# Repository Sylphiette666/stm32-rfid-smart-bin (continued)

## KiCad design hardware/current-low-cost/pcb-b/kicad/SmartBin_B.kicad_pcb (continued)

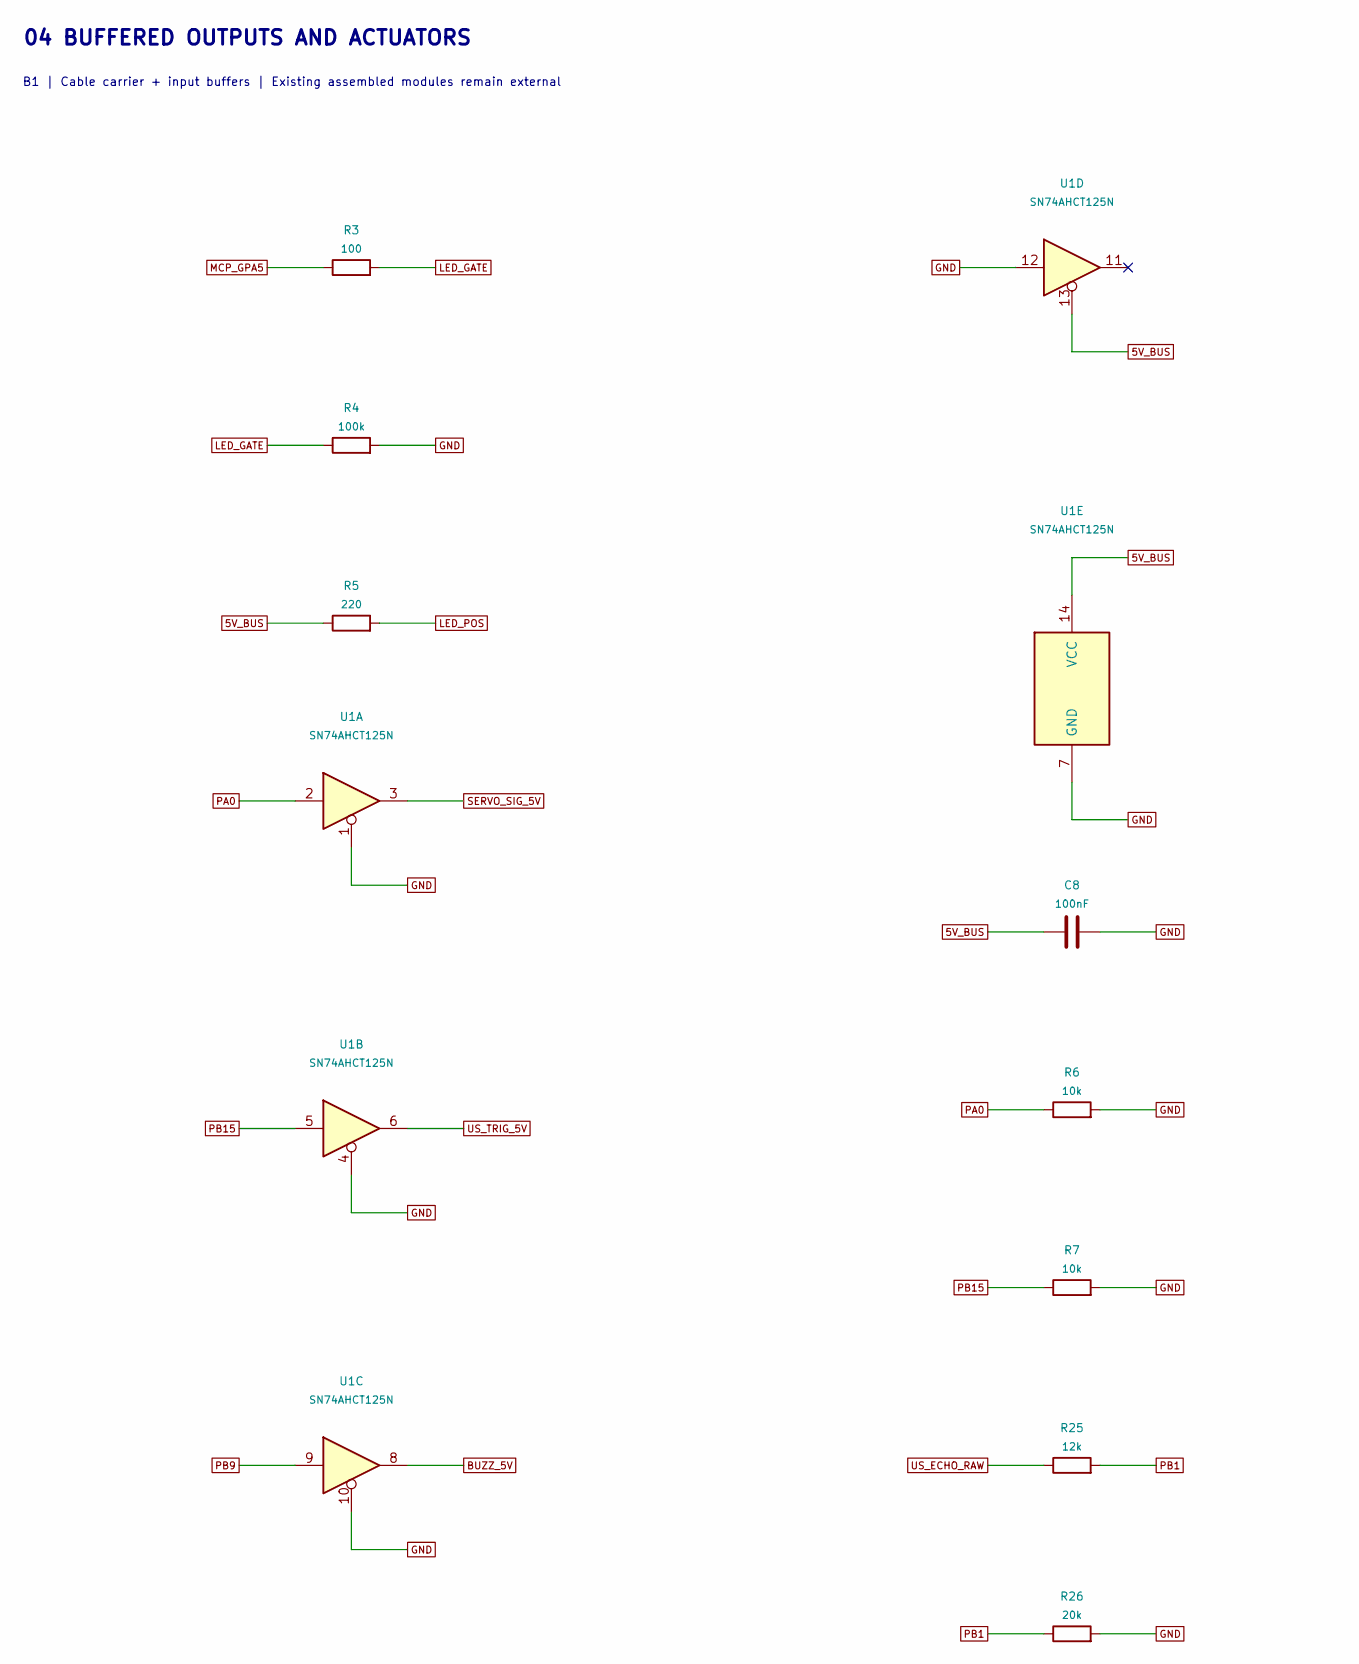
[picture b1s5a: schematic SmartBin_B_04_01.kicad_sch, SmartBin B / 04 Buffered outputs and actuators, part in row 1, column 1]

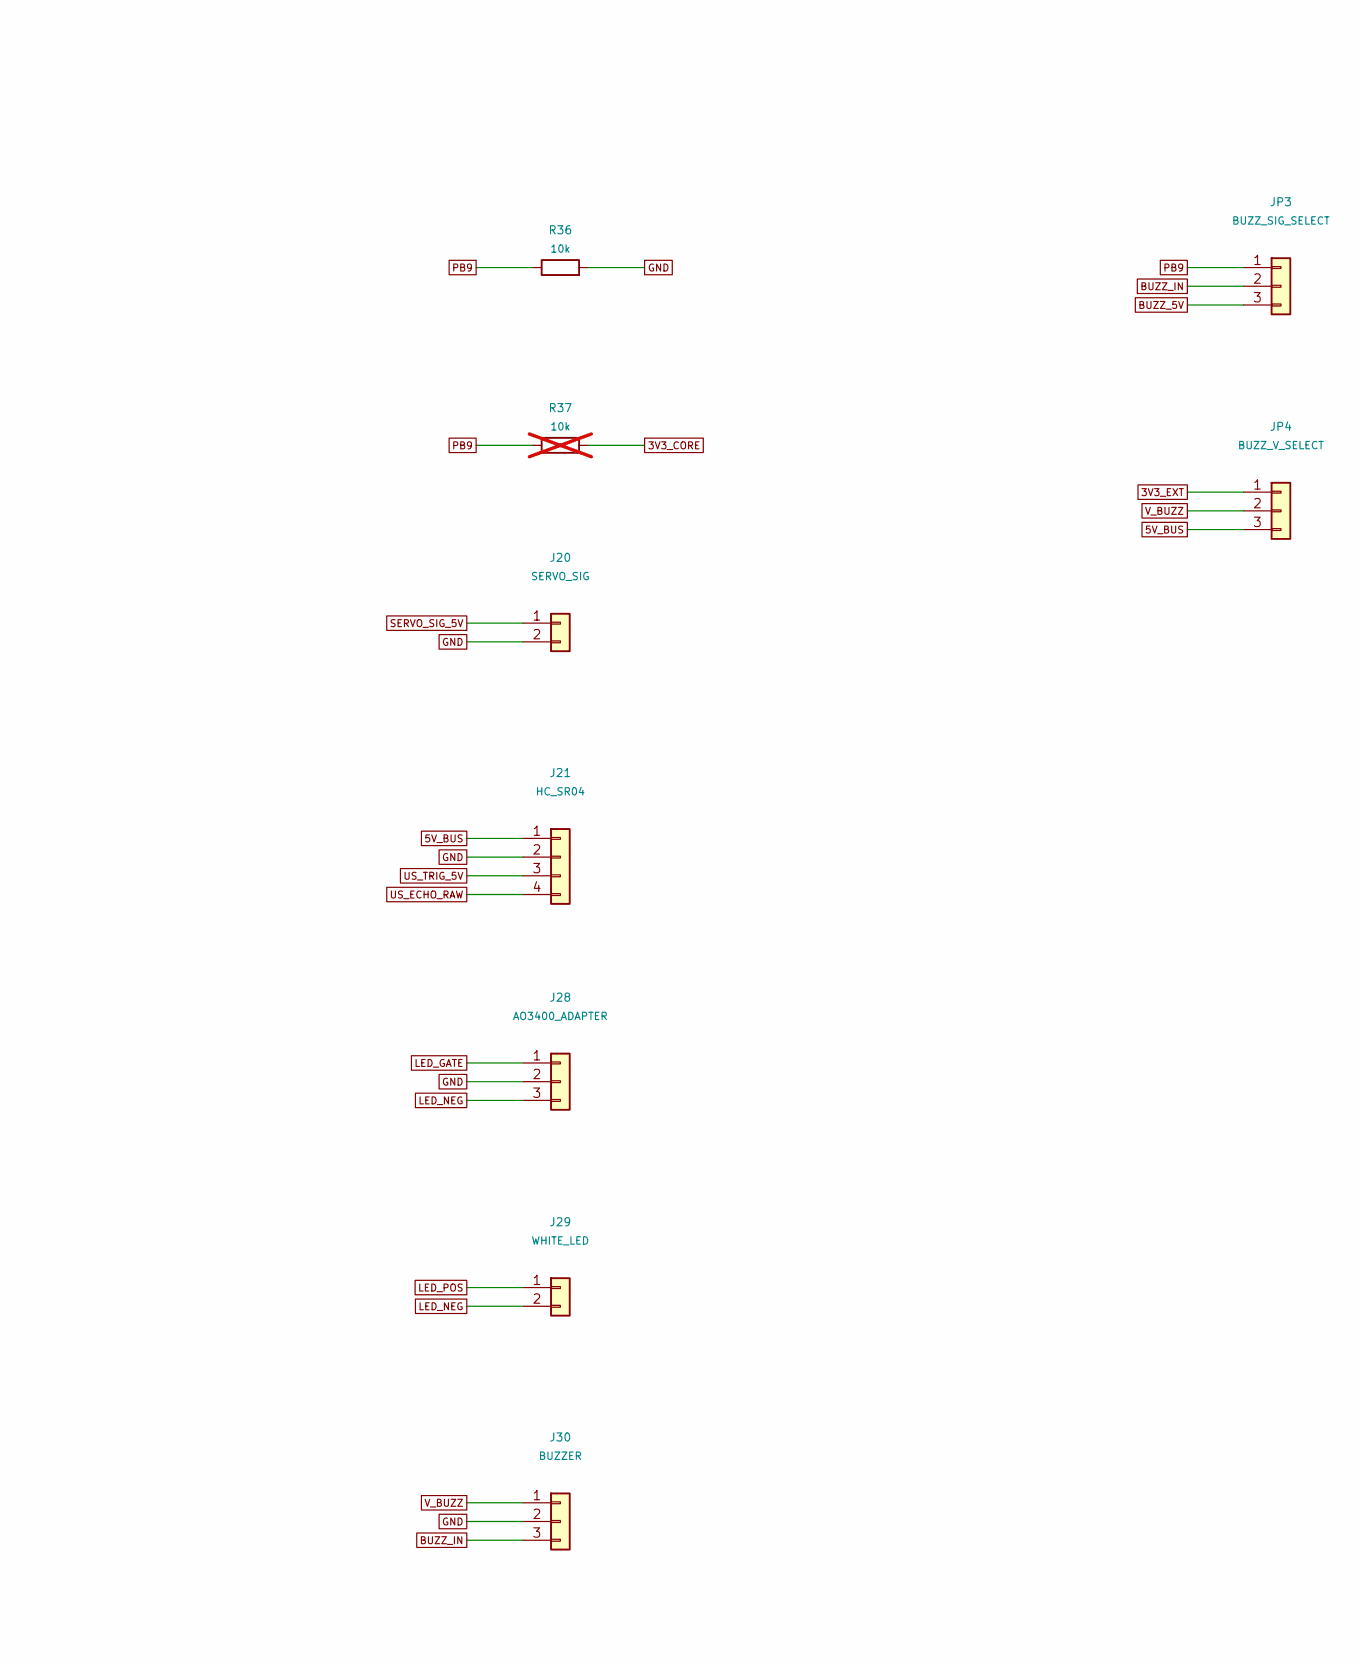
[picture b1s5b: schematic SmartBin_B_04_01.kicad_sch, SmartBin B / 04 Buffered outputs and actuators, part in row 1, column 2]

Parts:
C8: 100nF; C_Disc_D5.0mm_W2.5mm_P5.00mm
J20: SERVO_SIG; PinHeader_1x02_P2.54mm_Vertical
J21: HC_SR04; PinHeader_1x04_P2.54mm_Vertical
J28: AO3400_ADAPTER; PinHeader_1x03_P2.54mm_Vertical
J29: WHITE_LED; PinHeader_1x02_P2.54mm_Vertical
J30: BUZZER; PinHeader_1x03_P2.54mm_Vertical
JP3: BUZZ_SIG_SELECT; PinHeader_1x03_P2.54mm_Vertical
JP4: BUZZ_V_SELECT; PinHeader_1x03_P2.54mm_Vertical
R3: 100; R_Axial_DIN0207_L6.3mm_D2.5mm_P10.16mm_Horizontal
R4: 100k; R_Axial_DIN0207_L6.3mm_D2.5mm_P10.16mm_Horizontal
R5: 220; R_Axial_DIN0207_L6.3mm_D2.5mm_P10.16mm_Horizontal
R6, R7, R36: 10k; R_Axial_DIN0207_L6.3mm_D2.5mm_P10.16mm_Horizontal
R25: 12k; R_Axial_DIN0207_L6.3mm_D2.5mm_P10.16mm_Horizontal
R26: 20k; R_Axial_DIN0207_L6.3mm_D2.5mm_P10.16mm_Horizontal
R37: 10k; R_Axial_DIN0207_L6.3mm_D2.5mm_P10.16mm_Horizontal; not fitted
U1: SN74AHCT125N; DIP-14_W7.62mm_Socket

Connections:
3V3_CORE: R37.2; also elsewhere on the board
3V3_EXT: JP4.1; also elsewhere on the board
5V_BUS: C8.1, J21.1, JP4.3, R5.1, U1.13, U1.14 (VCC); also elsewhere on the board
BUZZ_5V: JP3.3, U1.8
BUZZ_IN: J30.3, JP3.2
GND: C8.2, J20.2, J21.2, J28.2, J30.2, R4.2, R6.2, R7.2, R26.2, R36.2, U1.1, U1.4, U1.7 (GND), U1.10, U1.12; also elsewhere on the board
LED_GATE: J28.1, R3.2, R4.1
LED_NEG: J28.3, J29.2
LED_POS: J29.1, R5.2
MCP_GPA5: R3.1; also elsewhere on the board
PA0: R6.1, U1.2; also elsewhere on the board
PB1: R25.2, R26.1; also elsewhere on the board
PB9: JP3.1, R36.1, R37.1, U1.9; also elsewhere on the board
PB15: R7.1, U1.5; also elsewhere on the board
SERVO_SIG_5V: J20.1, U1.3
US_ECHO_RAW: J21.4, R25.1
US_TRIG_5V: J21.3, U1.6
V_BUZZ: J30.1, JP4.2

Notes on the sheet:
04 BUFFERED OUTPUTS AND ACTUATORS
B1 | Cable carrier + input buffers | Existing assembled modules remain external

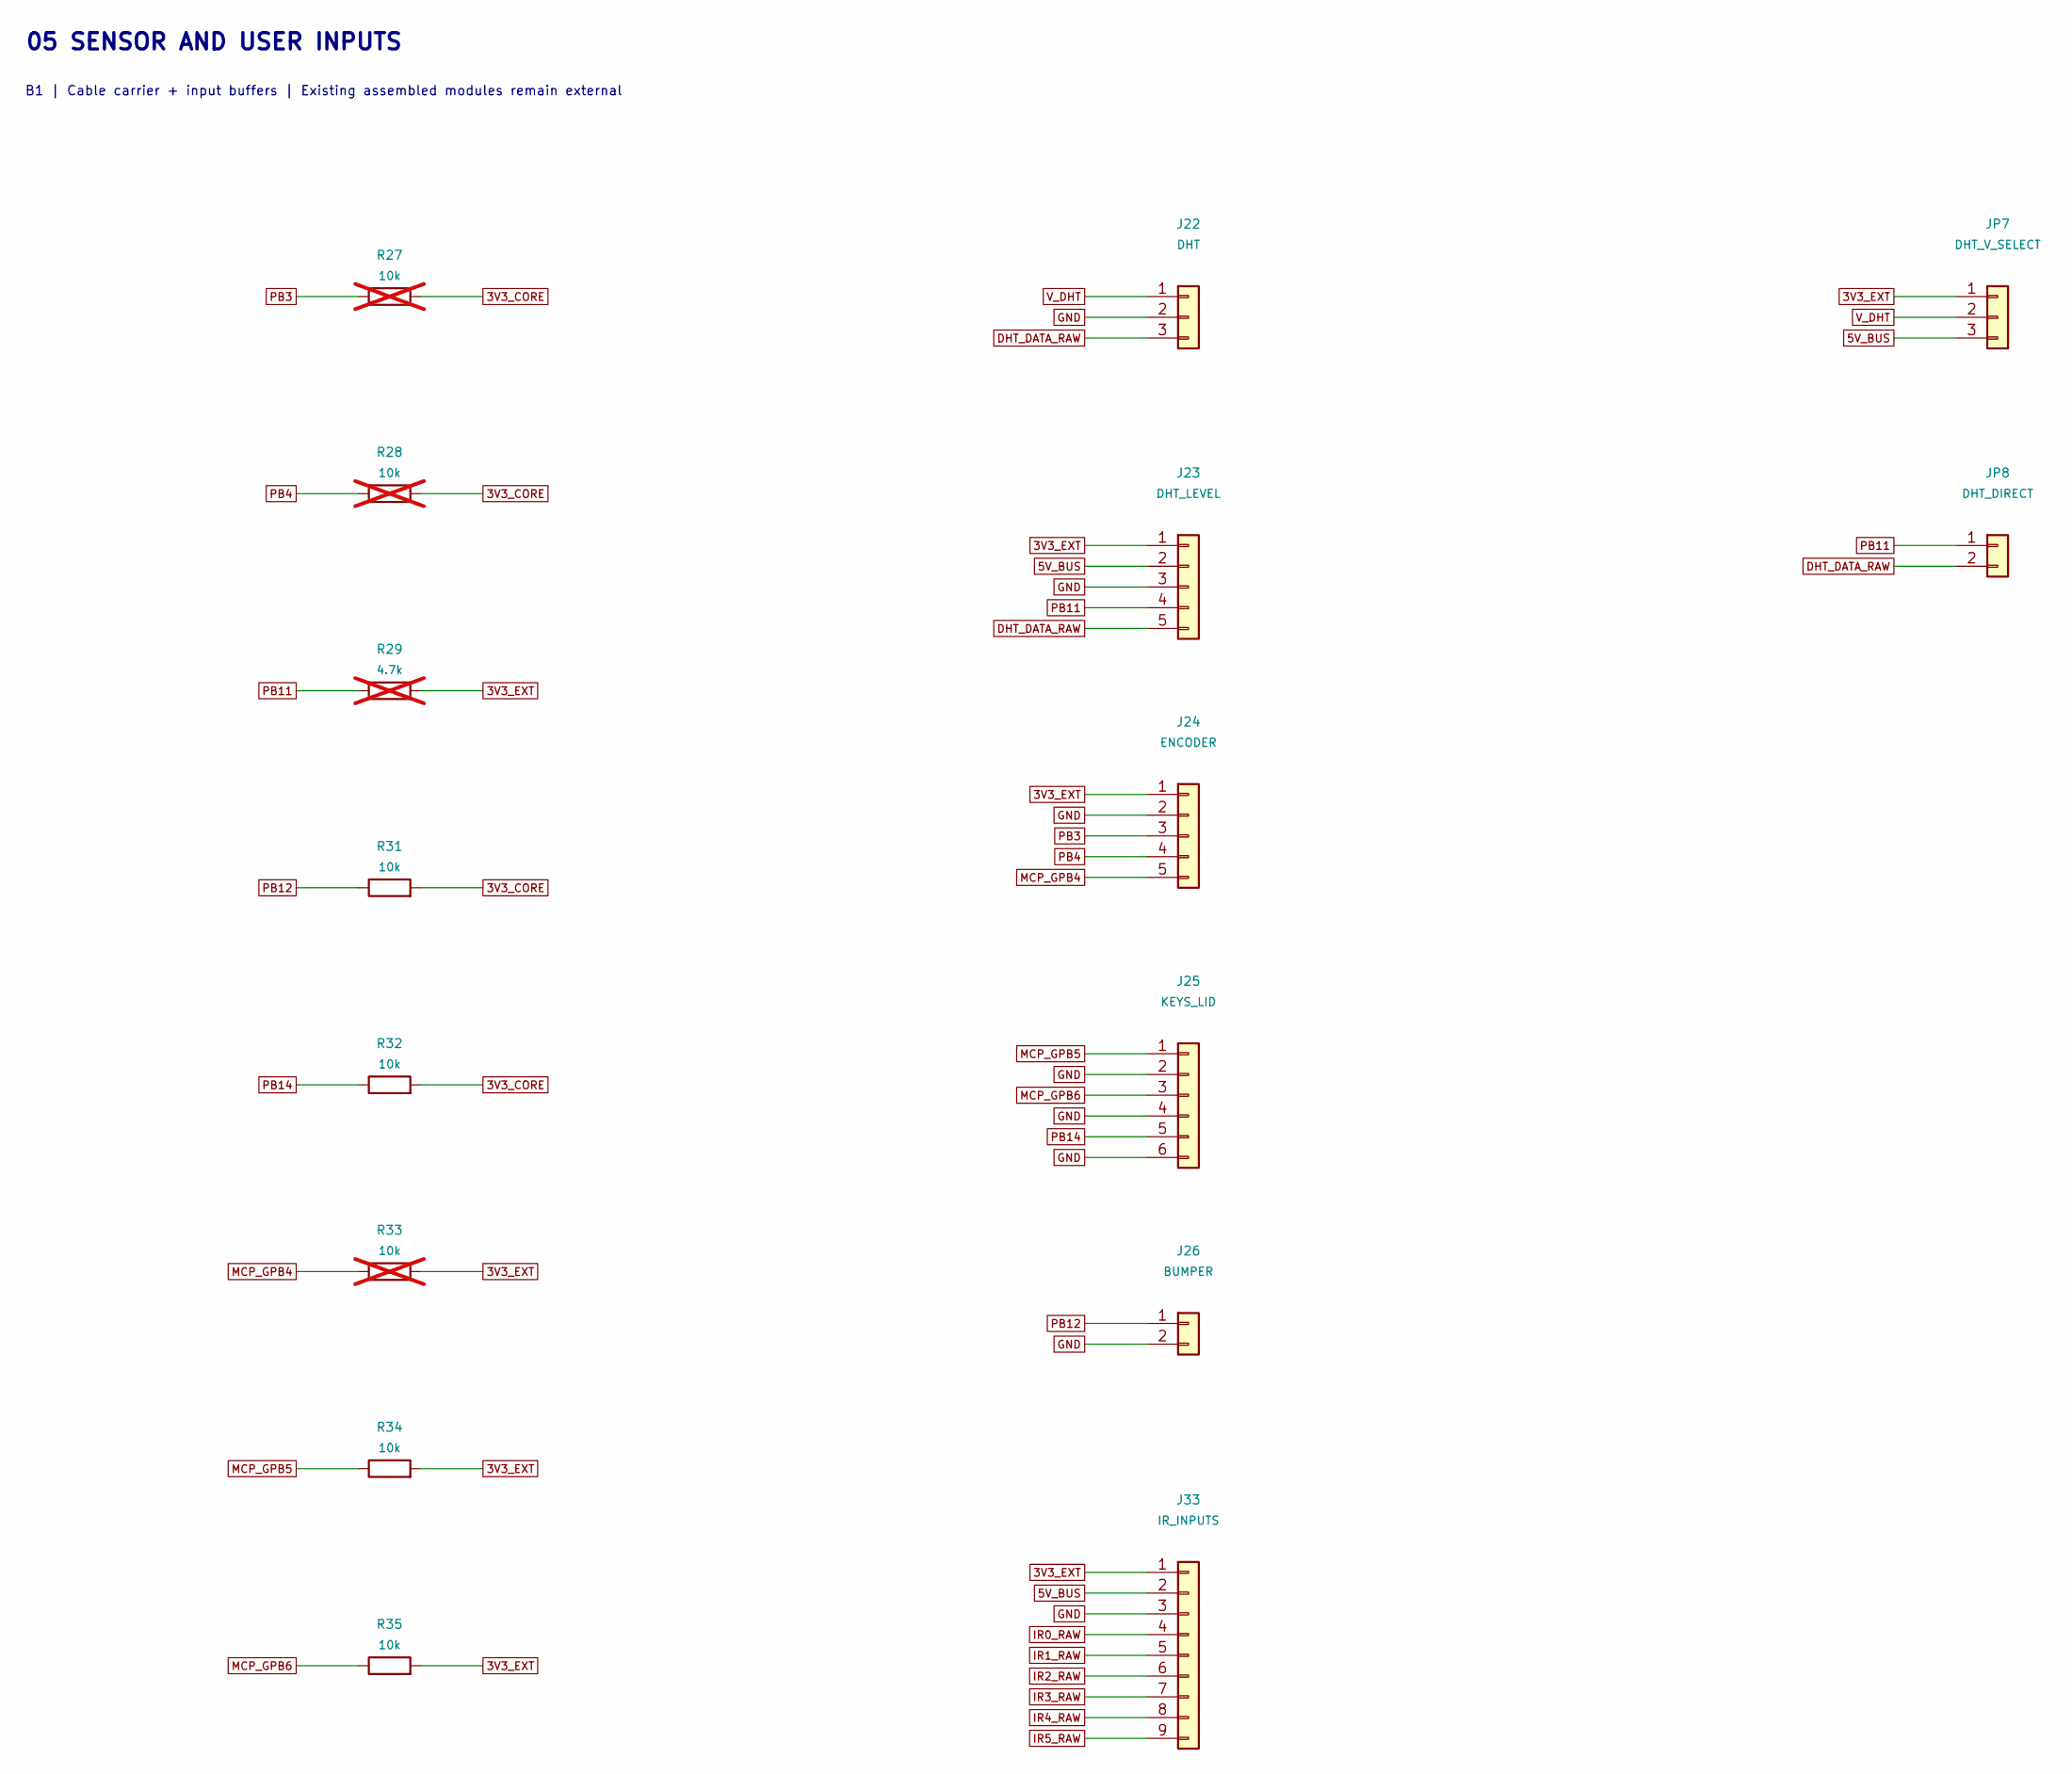
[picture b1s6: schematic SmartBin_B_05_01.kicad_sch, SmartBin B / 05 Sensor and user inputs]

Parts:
J22: DHT; PinHeader_1x03_P2.54mm_Vertical
J23: DHT_LEVEL; PinHeader_1x05_P2.54mm_Vertical
J24: ENCODER; PinHeader_1x05_P2.54mm_Vertical
J25: KEYS_LID; PinHeader_1x06_P2.54mm_Vertical
J26: BUMPER; PinHeader_1x02_P2.54mm_Vertical
J33: IR_INPUTS; PinHeader_1x09_P2.54mm_Vertical
JP7: DHT_V_SELECT; PinHeader_1x03_P2.54mm_Vertical
JP8: DHT_DIRECT; PinHeader_1x02_P2.54mm_Vertical
R27, R28, R33: 10k; R_Axial_DIN0207_L6.3mm_D2.5mm_P10.16mm_Horizontal; not fitted
R29: 4.7k; R_Axial_DIN0207_L6.3mm_D2.5mm_P10.16mm_Horizontal; not fitted
R31, R32, R34, R35: 10k; R_Axial_DIN0207_L6.3mm_D2.5mm_P10.16mm_Horizontal

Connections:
3V3_CORE: R27.2, R28.2, R31.2, R32.2; also elsewhere on the board
3V3_EXT: J23.1, J24.1, J33.1, JP7.1, R29.2, R33.2, R34.2, R35.2; also elsewhere on the board
5V_BUS: J23.2, J33.2, JP7.3; also elsewhere on the board
DHT_DATA_RAW: J22.3, J23.5, JP8.2
GND: J22.2, J23.3, J24.2, J25.2, J25.4, J25.6, J26.2, J33.3; also elsewhere on the board
IR0_RAW: J33.4; also elsewhere on the board
IR1_RAW: J33.5; also elsewhere on the board
IR2_RAW: J33.6; also elsewhere on the board
IR3_RAW: J33.7; also elsewhere on the board
IR4_RAW: J33.8; also elsewhere on the board
IR5_RAW: J33.9; also elsewhere on the board
MCP_GPB4: J24.5, R33.1; also elsewhere on the board
MCP_GPB5: J25.1, R34.1; also elsewhere on the board
MCP_GPB6: J25.3, R35.1; also elsewhere on the board
PB3: J24.3, R27.1; also elsewhere on the board
PB4: J24.4, R28.1; also elsewhere on the board
PB11: J23.4, JP8.1, R29.1; also elsewhere on the board
PB12: J26.1, R31.1; also elsewhere on the board
PB14: J25.5, R32.1; also elsewhere on the board
V_DHT: J22.1, JP7.2

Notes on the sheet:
05 SENSOR AND USER INPUTS
B1 | Cable carrier + input buffers | Existing assembled modules remain external

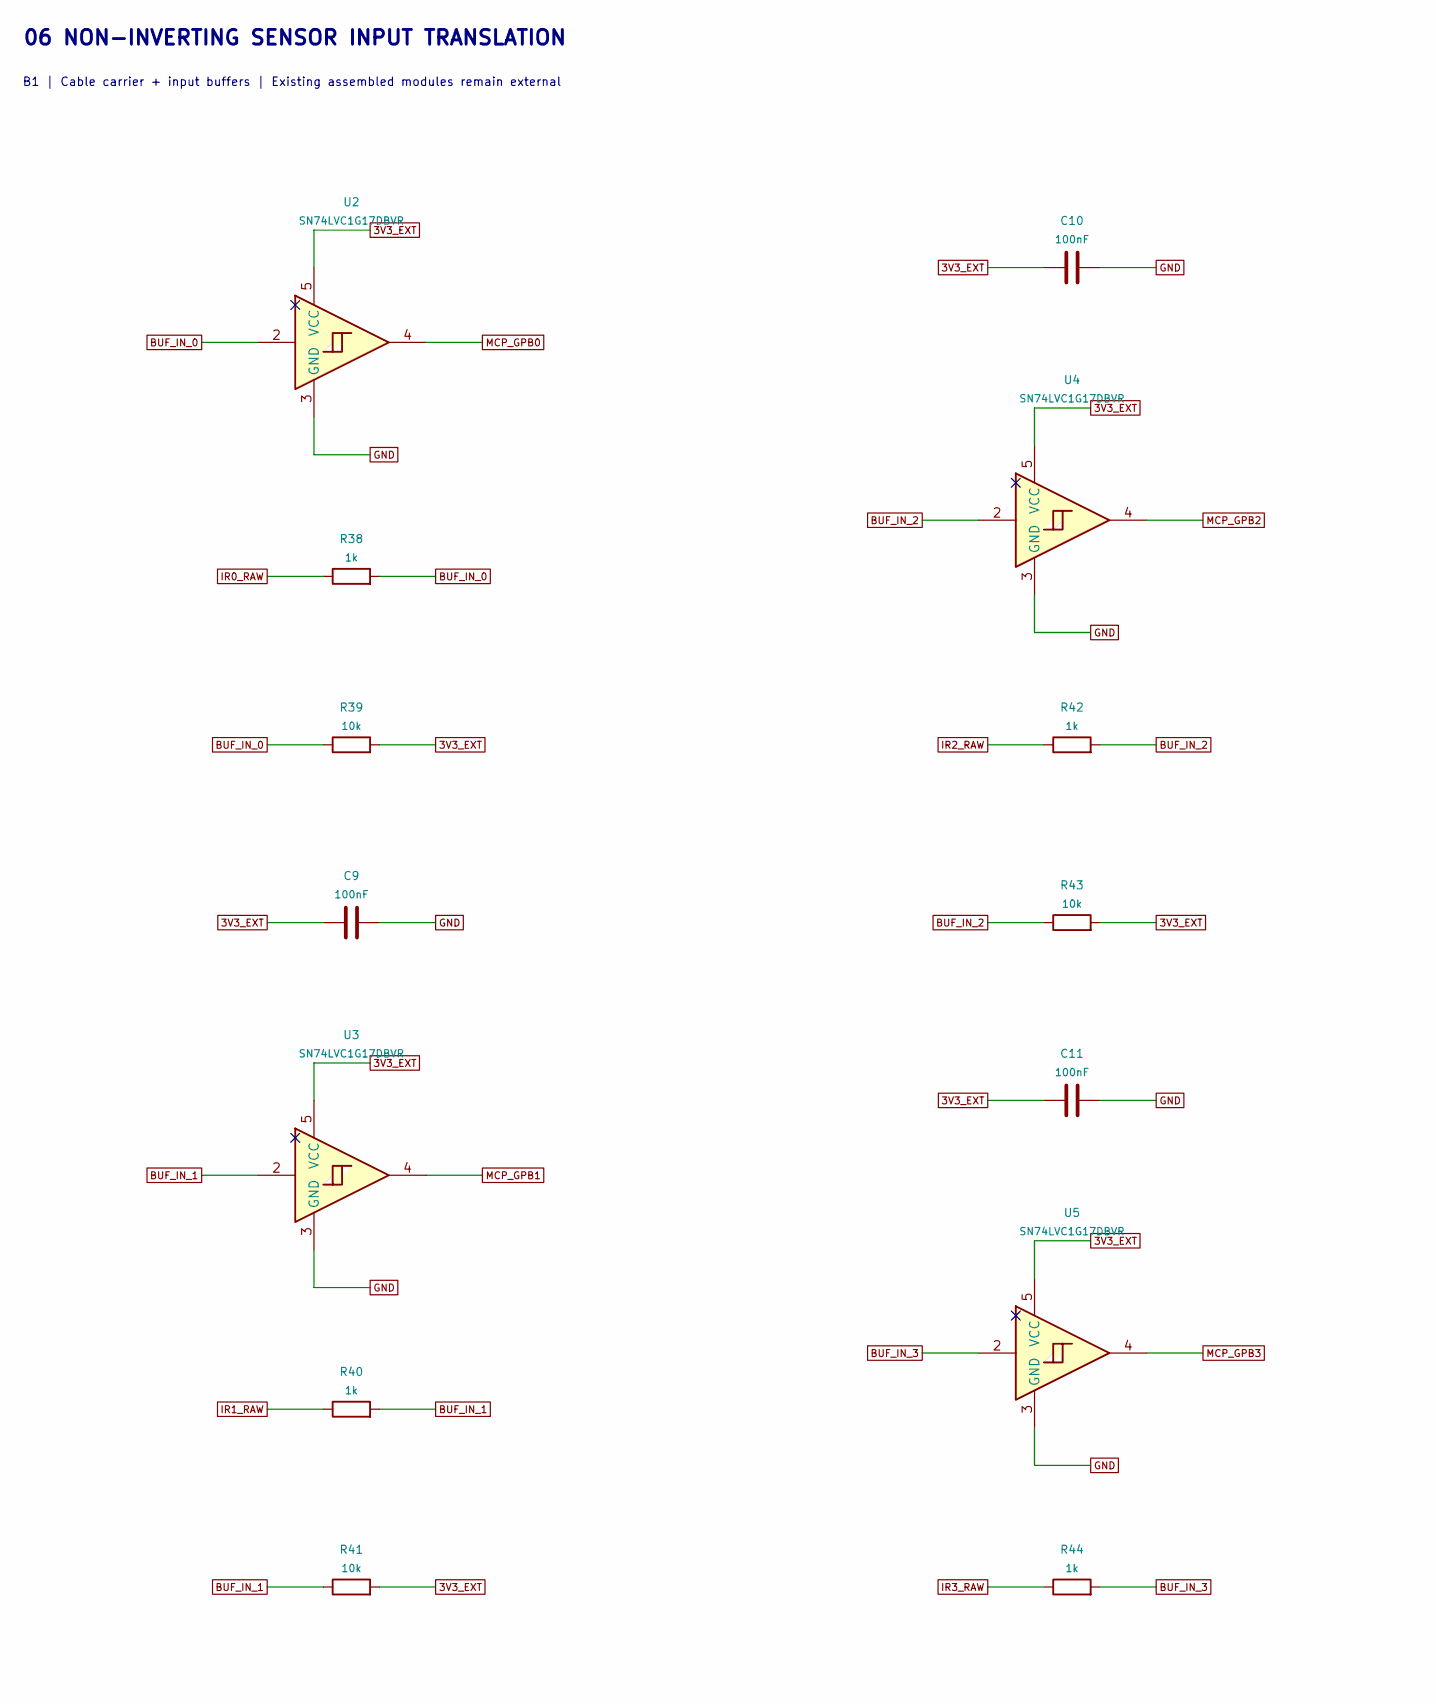
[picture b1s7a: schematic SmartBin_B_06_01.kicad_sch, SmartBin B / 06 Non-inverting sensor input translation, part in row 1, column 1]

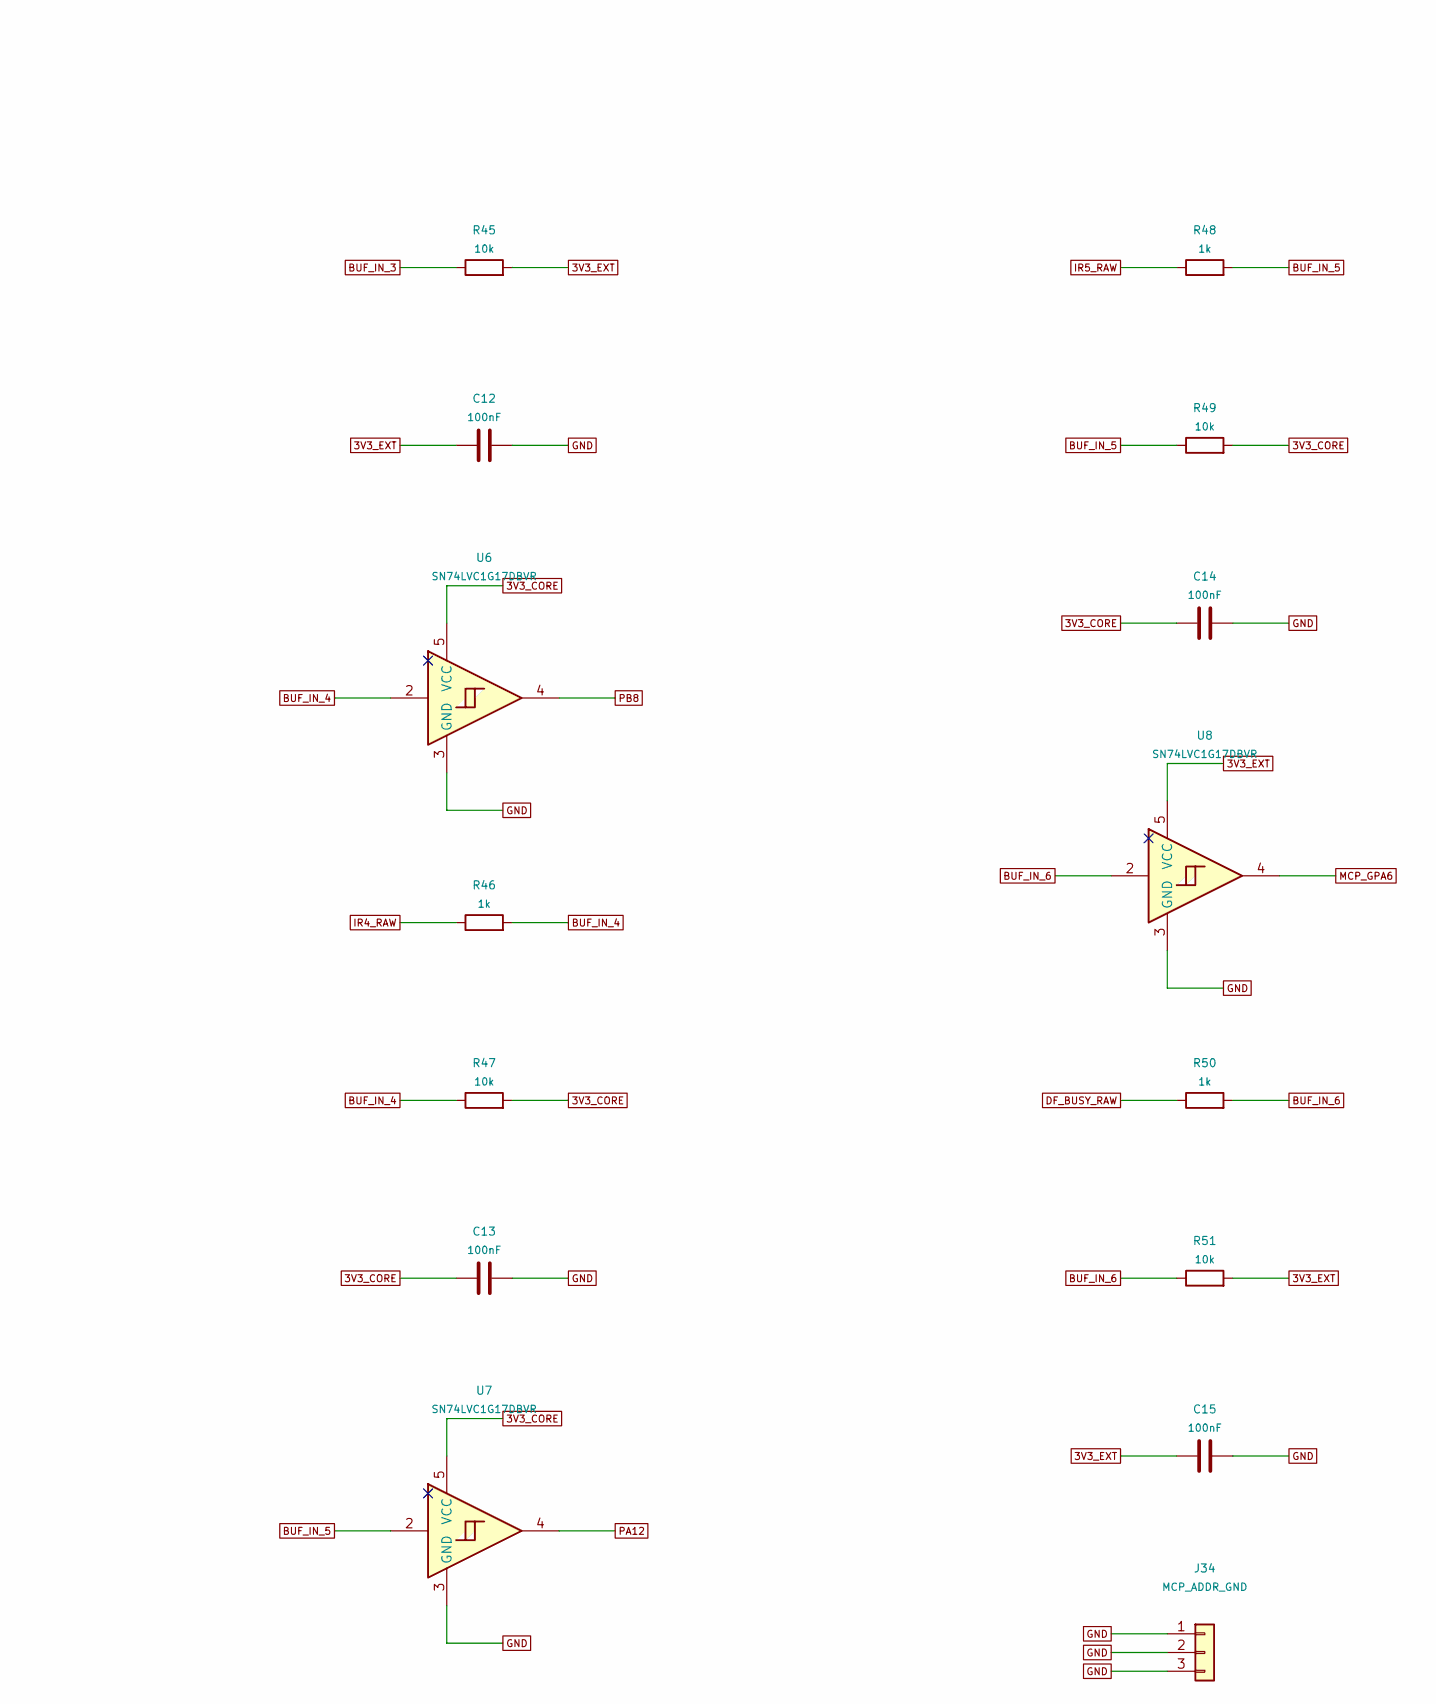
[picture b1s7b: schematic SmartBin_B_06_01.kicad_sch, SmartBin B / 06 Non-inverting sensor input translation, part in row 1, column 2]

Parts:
C9, C10, C11, C12, C13, C14, C15: 100nF; C_0805_2012Metric
J34: MCP_ADDR_GND; PinHeader_1x03_P2.54mm_Vertical
R38, R40, R42, R44, R46, R48, R50: 1k; R_0805_2012Metric
R39, R41, R43, R45, R47, R49, R51: 10k; R_0805_2012Metric
U2, U3, U4, U5, U6, U7, U8: SN74LVC1G17DBVR; SOT-23-5; MPN SN74LVC1G17DBVR

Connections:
3V3_CORE: C13.1, C14.1, R47.2, R49.2, U6.5 (VCC), U7.5 (VCC); also elsewhere on the board
3V3_EXT: C9.1, C10.1, C11.1, C12.1, C15.1, R39.2, R41.2, R43.2, R45.2, R51.2, U2.5 (VCC), U3.5 (VCC), U4.5 (VCC), U5.5 (VCC), U8.5 (VCC); also elsewhere on the board
BUF_IN_0: R38.2, R39.1, U2.2
BUF_IN_1: R40.2, R41.1, U3.2
BUF_IN_2: R42.2, R43.1, U4.2
BUF_IN_3: R44.2, R45.1, U5.2
BUF_IN_4: R46.2, R47.1, U6.2
BUF_IN_5: R48.2, R49.1, U7.2
BUF_IN_6: R50.2, R51.1, U8.2
DF_BUSY_RAW: R50.1; also elsewhere on the board
GND: C9.2, C10.2, C11.2, C12.2, C13.2, C14.2, C15.2, J34.1, J34.2, J34.3, U2.3 (GND), U3.3 (GND), U4.3 (GND), U5.3 (GND), U6.3 (GND), U7.3 (GND), U8.3 (GND); also elsewhere on the board
IR0_RAW: R38.1; also elsewhere on the board
IR1_RAW: R40.1; also elsewhere on the board
IR2_RAW: R42.1; also elsewhere on the board
IR3_RAW: R44.1; also elsewhere on the board
IR4_RAW: R46.1; also elsewhere on the board
IR5_RAW: R48.1; also elsewhere on the board
MCP_GPA6: U8.4; also elsewhere on the board
MCP_GPB0: U2.4; also elsewhere on the board
MCP_GPB1: U3.4; also elsewhere on the board
MCP_GPB2: U4.4; also elsewhere on the board
MCP_GPB3: U5.4; also elsewhere on the board
PA12: U7.4; also elsewhere on the board
PB8: U6.4; also elsewhere on the board

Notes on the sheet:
06 NON-INVERTING SENSOR INPUT TRANSLATION
B1 | Cable carrier + input buffers | Existing assembled modules remain external

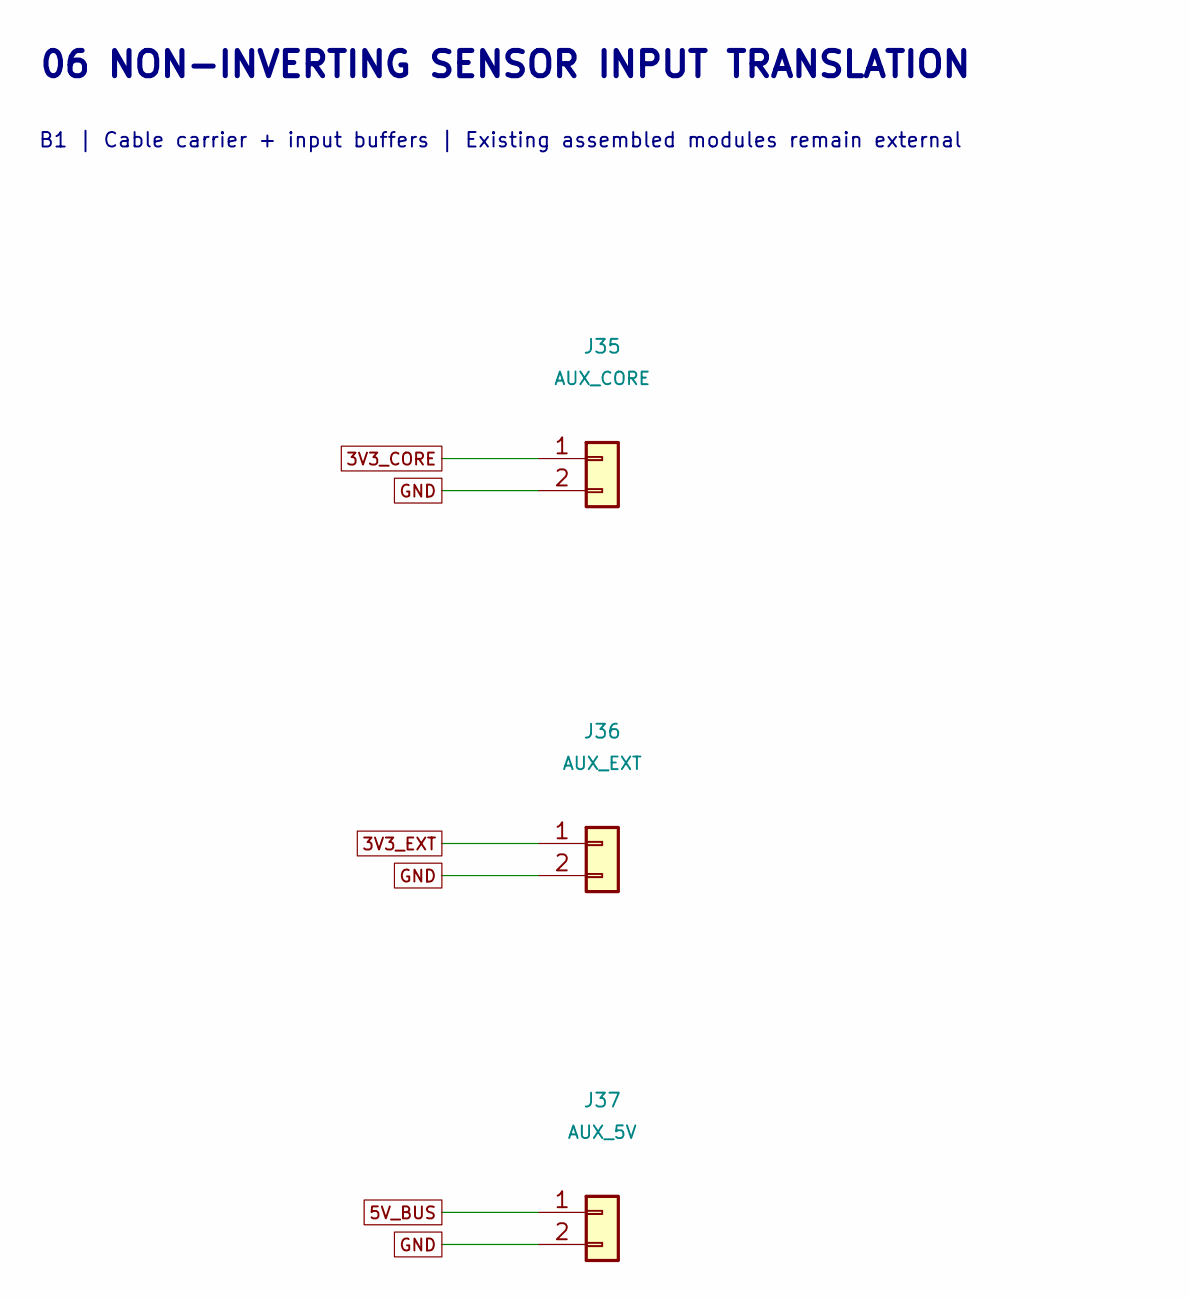
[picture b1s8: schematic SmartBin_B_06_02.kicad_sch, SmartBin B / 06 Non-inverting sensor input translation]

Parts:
J35: AUX_CORE; PinHeader_1x02_P2.54mm_Vertical
J36: AUX_EXT; PinHeader_1x02_P2.54mm_Vertical
J37: AUX_5V; PinHeader_1x02_P2.54mm_Vertical

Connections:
3V3_CORE: J35.1; also elsewhere on the board
3V3_EXT: J36.1; also elsewhere on the board
5V_BUS: J37.1; also elsewhere on the board
GND: J35.2, J36.2, J37.2; also elsewhere on the board

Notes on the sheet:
06 NON-INVERTING SENSOR INPUT TRANSLATION
B1 | Cable carrier + input buffers | Existing assembled modules remain external

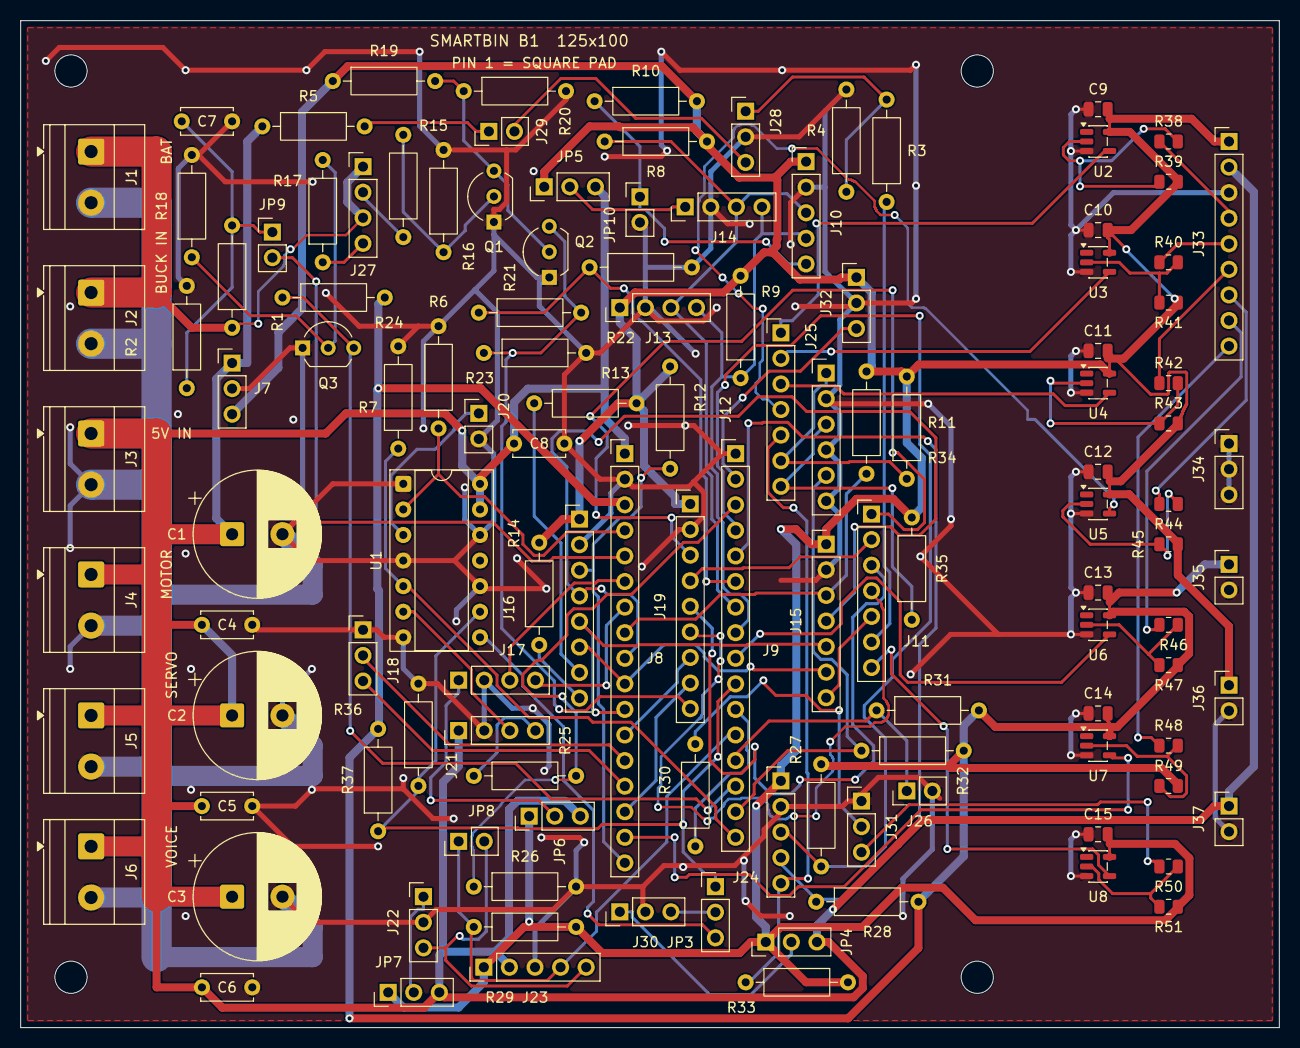
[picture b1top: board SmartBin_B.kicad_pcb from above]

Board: 2 copper layers, 125.0 x 100.0 mm, 126 parts (0 on the bottom side), 86 nets.
